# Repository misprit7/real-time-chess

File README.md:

<h1 align="center">
  <!--<picture></picture>-->
  <br />
  Real Time Chess
</h1>
<h2 align="center">
  A physical chess board without the concept of turns
</h2>
<h2 align="center">
  Video explanation: https://youtu.be/y7VtSK23_Jg
</h2>

# Pitch

Chess is boring. I'm boring too so I enjoy it anyways, but I can't help but think "I could design it better." Normally in chess players move sequentially in turns, but this introduces a huge latency bug that the developers of chess forgot to patch: you spend literally half the time waiting for your opponent!

The obvious solution is just get rid of the concept of turns in chess altogether and let players move whenever they want. Real time strategy games like StarCraft and Age of Empires are much more fun and spectator friendly than chess, so this should be a pretty uncontroversial minor rules update that can be implemented before the next world championship. To prevent things from getting too chaotic over the board each piece has an individual cooldown, so once it's been moved it can't move for a fixed period afterwards.

However there's an unfortunate roadblock to the widespread adoption of real time chess: as the [Niemann controversy](https://www.cnn.com/2023/09/26/sport/hans-niemann-denies-sex-toys-cheating-chess-spt-intl/index.html) has made all too clear, chess is [not immune](https://www.youtube.com/watch?v=QNuu8KTUEwU) from accusations of cheating through spectator **ass**istance or outside **anal**isys tools. Trying to have players self enforce these piece cooldowns is impossible. However where the intrinsic goodness of the human psyche fails, engineering is always ready to step in. This project is a physical chess board that keeps track and displays the cooldown remaining for each piece, and even physically holds them in place so no accidental cheating can occur.

# Design Files

The firmware and pcb kicad files are in this repo. For the physical design, see [the design on OnShape](https://cad.onshape.com/documents/ad9a4c8f8eed1cb460895551/w/e793072796f18b5ae284597f/e/b7ae406cfa566c5c0e6fed4b). Other than those parts that were cnced, here were the off the shelf components used:

- [Insulating washers](https://www.mcmaster.com/catalog/130/3683/95225A340): One under each electromagnet, to keep them isolated from the casing
- [Plastic screws](https://www.mcmaster.com/catalog/130/3446/92492A728): To attach electromagnets to base, plastic to prevent electrical connection
- [These](https://www.mcmaster.com/catalog/130/3435/92095A182) and [these](https://www.mcmaster.com/catalog/130/3435/92095A177) screws: to attach the internal supports and squares respectively
- [Spacers](https://www.mcmaster.com/catalog/94669A095): For an offset between the decorative and functional pcbs
- [Electromagnets](https://www.adafruit.com/product/3873): Most expensive part other than the machining, ~$600 per board. Could probably get them cheaper from China or something but for low quantities this was easiest

# Known Issues

- Power distribution: Traces on the pcbs are way undersized given there are many amps running through them, so there are large voltage drops when many pieces are on cooldown simultaneously. To solve this these traces should be much wider
- Tolerances: The pcbs have extremely tight tolerances which makes assmbling the board extremely annoying. The edges and holes should probably have more room
- Pin heights: The height of the pins for the banana connectors are taller than the mechanical design allows for, these are fairly easy to shorten using a dremel but probably something that should be fixed
- Corner screws: Given the order of assembly, it's impossible to insert/fasten the 4 corner screws

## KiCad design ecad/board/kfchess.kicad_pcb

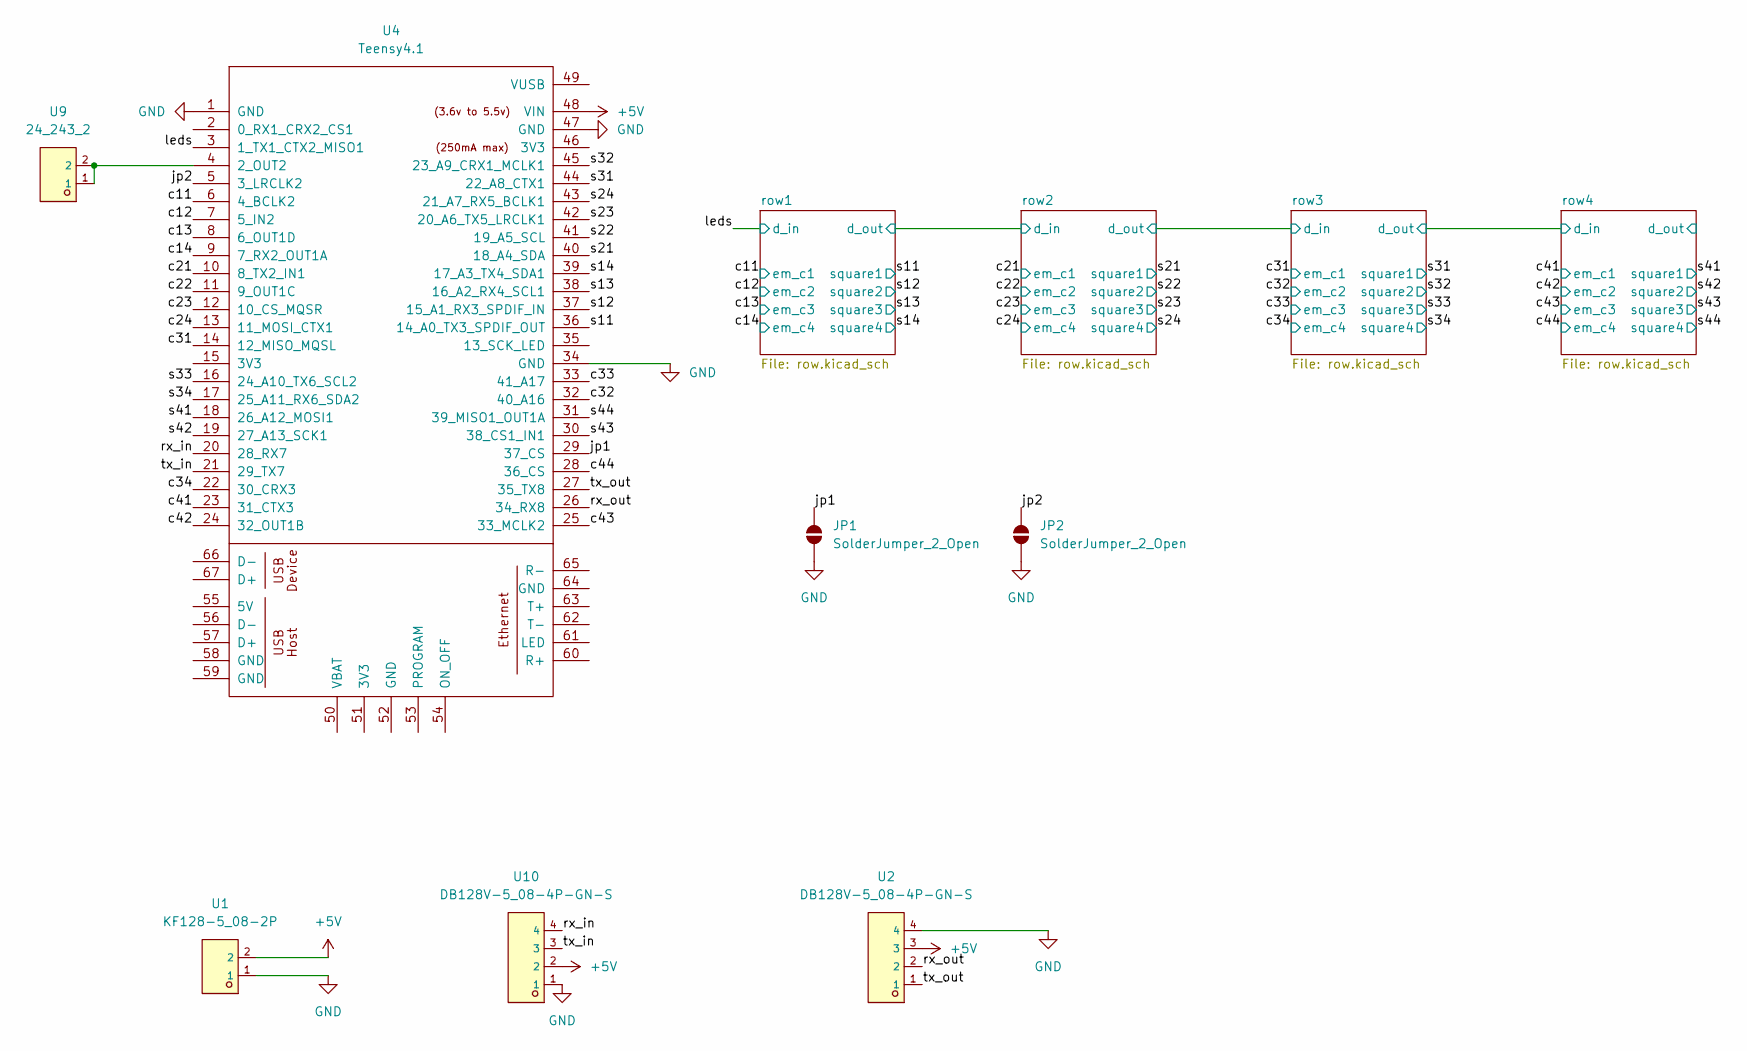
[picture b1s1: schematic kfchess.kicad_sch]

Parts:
JP1, JP2: SolderJumper_2_Open; SolderJumper-2_P1.3mm_Open_Pad1.0x1.5mm
U1: KF128-5_08-2P; CONN-TH_P5.08_KF128-5.08-2P; LCSC C474952
U2, U10: DB128V-5_08-4P-GN-S; CONN-TH_4P-P5.08_DIBO_DB128V-5.08; LCSC C2915641
U4: Teensy4.1; Teensy41
U9: 24_243_2; CONN-TH_24.243.2; LCSC C7437322

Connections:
+5V: U1.2, U2.3, U4.48 (VIN), U10.2; also elsewhere on the board
/c11: U4.6 (4_BCLK2); also elsewhere on the board
/c12: U4.7 (5_IN2); also elsewhere on the board
/c13: U4.8 (6_OUT1D); also elsewhere on the board
/c14: U4.9 (7_RX2_OUT1A); also elsewhere on the board
/c21: U4.10 (8_TX2_IN1); also elsewhere on the board
/c22: U4.11 (9_OUT1C); also elsewhere on the board
/c23: U4.12 (10_CS_MQSR); also elsewhere on the board
/c24: U4.13 (11_MOSI_CTX1); also elsewhere on the board
/c31: U4.14 (12_MISO_MQSL); also elsewhere on the board
/c32: U4.32 (40_A16); also elsewhere on the board
/c33: U4.33 (41_A17); also elsewhere on the board
/c34: U4.22 (30_CRX3); also elsewhere on the board
/c41: U4.23 (31_CTX3); also elsewhere on the board
/c42: U4.24 (32_OUT1B); also elsewhere on the board
/c43: U4.25 (33_MCLK2); also elsewhere on the board
/c44: U4.28 (36_CS); also elsewhere on the board
/jp1: JP1.2 (B), U4.29 (37_CS)
/jp2: JP2.2 (B), U4.5 (3_LRCLK2)
/leds: U4.3 (1_TX1_CTX2_MISO1); also elsewhere on the board
/rx_in: U4.20 (28_RX7), U10.4
/rx_out: U2.2, U4.26 (34_RX8)
/s11: U4.36 (14_A0_TX3_SPDIF_OUT); also elsewhere on the board
/s13: U4.38 (16_A2_RX4_SCL1); also elsewhere on the board
/s14: U4.39 (17_A3_TX4_SDA1); also elsewhere on the board
/s21: U4.40 (18_A4_SDA); also elsewhere on the board
/s22: U4.41 (19_A5_SCL); also elsewhere on the board
/s24: U4.43 (21_A7_RX5_BCLK1); also elsewhere on the board
/s31: U4.44 (22_A8_CTX1); also elsewhere on the board
/s32: U4.45 (23_A9_CRX1_MCLK1); also elsewhere on the board
/s33: U4.16 (24_A10_TX6_SCL2); also elsewhere on the board
/s34: U4.17 (25_A11_RX6_SDA2); also elsewhere on the board
/s41: U4.18 (26_A12_MOSI1); also elsewhere on the board
/s42: U4.19 (27_A13_SCK1); also elsewhere on the board
/s43: U4.30 (38_CS1_IN1); also elsewhere on the board
/s44: U4.31 (39_MISO1_OUT1A); also elsewhere on the board
/tx_in: U4.21 (29_TX7), U10.3
/tx_out: U2.1, U4.27 (35_TX8)
GND: JP1.1 (A), JP2.1 (A), U1.1, U2.4, U4.1 (GND), U4.34 (GND), U4.47 (GND), U10.1; also elsewhere on the board
unnamed: U4.4 (2_OUT2), U9.1, U9.2

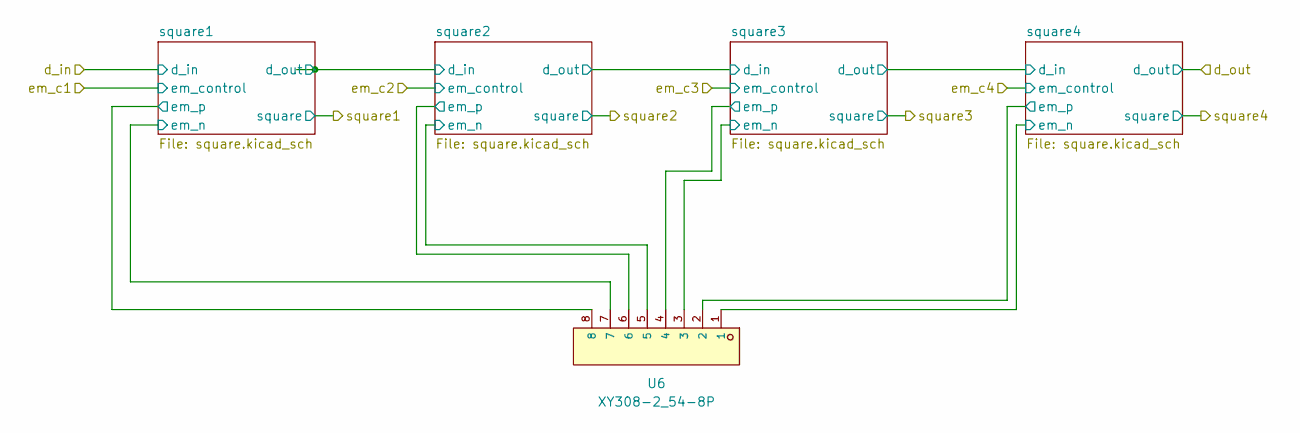
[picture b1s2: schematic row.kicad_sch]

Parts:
U6: XY308-2_54-8P; CONN-TH_XY308-2.54-8P; LCSC C915917

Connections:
+5V: U6.2, U6.4, U6.6, U6.8; also elsewhere on the board
/row2/square1/em_n: U6.7; also elsewhere on the board
/row2/square2/em_n: U6.5; also elsewhere on the board
/row2/square4/em_n: U6.1; also elsewhere on the board

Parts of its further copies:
U5, U7, U8: XY308-2_54-8P; CONN-TH_XY308-2.54-8P; LCSC C915917

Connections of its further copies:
+5V: U5.2, U5.4, U5.6, U5.8, U7.2, U7.4, U7.6, U7.8, U8.2, U8.4, U8.6, U8.8; also elsewhere on the board
/row1/square1/em_n: U5.7; also elsewhere on the board
/row1/square3/em_n: U5.3; also elsewhere on the board
/row1/square4/em_n: U5.1; also elsewhere on the board
/row3/square1/em_n: U7.7; also elsewhere on the board
/row3/square2/em_n: U7.5; also elsewhere on the board
/row3/square3/em_n: U7.3; also elsewhere on the board
/row3/square4/em_n: U7.1; also elsewhere on the board
/row4/square1/em_n: U8.7; also elsewhere on the board
/row4/square2/em_n: U8.5; also elsewhere on the board
/row4/square3/em_n: U8.3; also elsewhere on the board
/row4/square4/em_n: U8.1; also elsewhere on the board

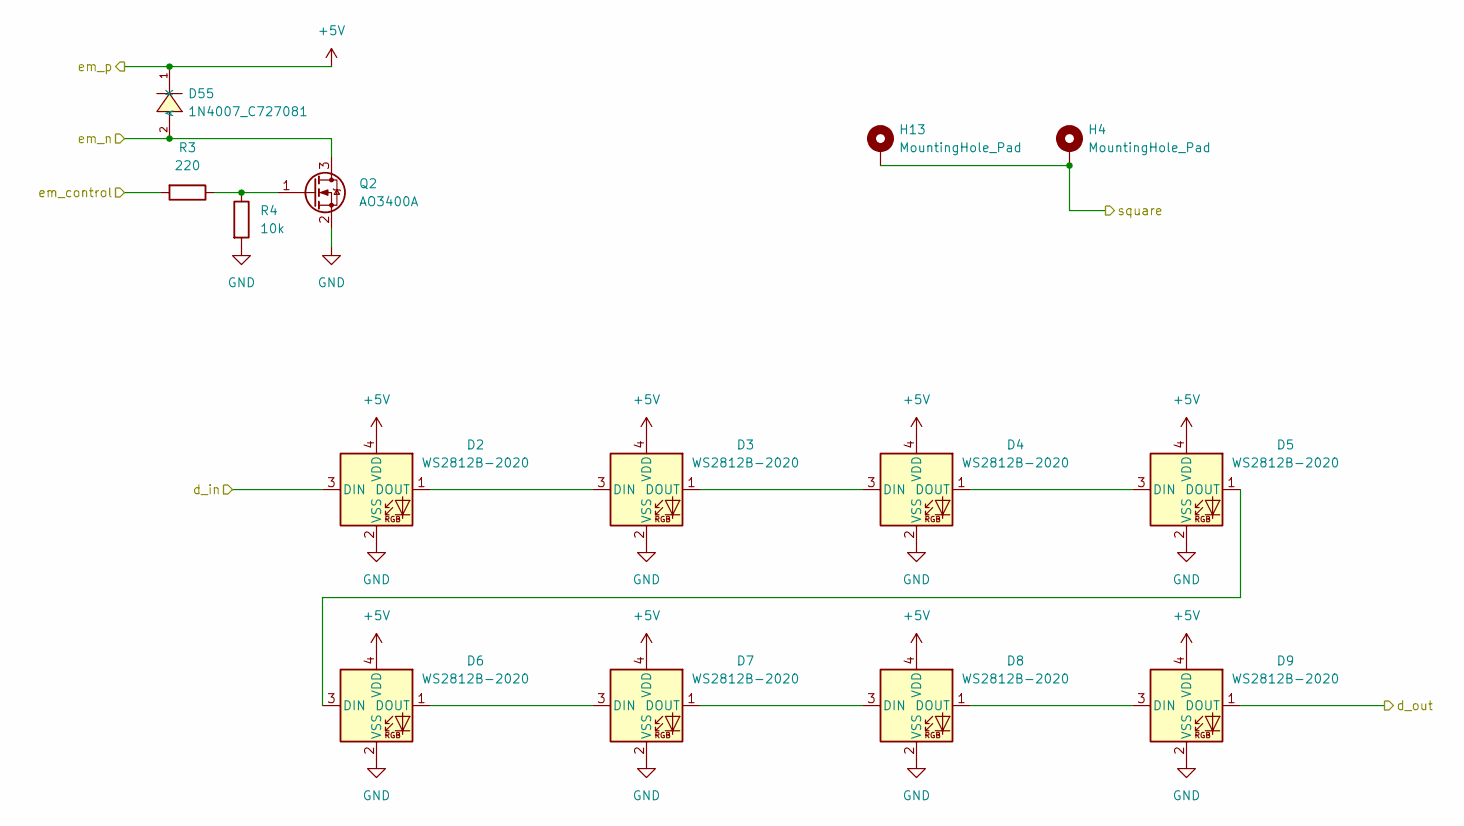
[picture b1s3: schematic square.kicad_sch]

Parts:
D2, D3, D4, D5, D6, D7, D8, D9: WS2812B-2020; LED_WS2812B-2020_PLCC4_2.0x2.0mm
D55: 1N4007_C727081; SMA_L4.3-W2.5-LS5.0-RD; LCSC C727081
H4, H13: MountingHole_Pad; MountingHole_3.2mm_M3_Pad
Q2: AO3400A; SOT-23
R3: 220; R_0603_1608Metric
R4: 10k; R_0603_1608Metric

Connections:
+5V: D2.4 (VDD), D3.4 (VDD), D4.4 (VDD), D5.4 (VDD), D6.4 (VDD), D7.4 (VDD), D8.4 (VDD), D9.4 (VDD), D55.1 (K); also elsewhere on the board
/c12: R3.2; also elsewhere on the board
/leds: D2.3 (DIN); also elsewhere on the board
/row1/square1/d_out: D9.1 (DOUT); also elsewhere on the board
GND: D2.2 (VSS), D3.2 (VSS), D4.2 (VSS), D5.2 (VSS), D6.2 (VSS), D7.2 (VSS), D8.2 (VSS), D9.2 (VSS), Q2.2 (S), R4.2; also elsewhere on the board
unnamed: D2.1 (DOUT), D3.3 (DIN)
unnamed: D3.1 (DOUT), D4.3 (DIN)
unnamed: D4.1 (DOUT), D5.3 (DIN)
unnamed: D5.1 (DOUT), D6.3 (DIN)
unnamed: D6.1 (DOUT), D7.3 (DIN)
unnamed: D7.1 (DOUT), D8.3 (DIN)
unnamed: D8.1 (DOUT), D9.3 (DIN)
unnamed: Q2.1 (G), R3.1, R4.1

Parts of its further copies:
D1, D10, D19, D28, D37, D46, D64, D73, D82, D91, D100, D109, D118, D127, D136: 1N4007_C727081; SMA_L4.3-W2.5-LS5.0-RD; LCSC C727081
D11, D12, D13, D14, D15, D16, D17, D18, D20, D21, D22, D23, D24, D25, D26, D27, D29, D30, D31, D32, D33, D34, D35, D36, D38, D39, D40, D41, D42, D43, D44, D45, D47, D48, D49, D50, D51, D52, D53, D54, D56, D57, D58, D59, D60, D61, D62, D63, D65, D66, D67, D68, D69, D70, D71, D72, D74, D75, D76, D77, D78, D79, D80, D81, D83, D84, D85, D86, D87, D88, D89, D90, D92, D93, D94, D95, D96, D97, D98, D99, D101, D102, D103, D104, D105, D106, D107, D108, D110, D111, D112, D113, D114, D115, D116, D117, D119, D120, D121, D122, D123, D124, D125, D126, D128, D129, D130, D131, D132, D133, D134, D135, D137, D138, D139, D140, D141, D142, D143, D144: WS2812B-2020; LED_WS2812B-2020_PLCC4_2.0x2.0mm
H1, H2, H3, H5, H6, H7, H8, H9, H10, H11, H12, H14, H15, H16, H17, H18, H19, H20, H21, H22, H23, H24, H25, H26, H27, H28, H29, H30, H31, H32: MountingHole_Pad; MountingHole_3.2mm_M3_Pad
Q1, Q3, Q4, Q5, Q6, Q7, Q8, Q9, Q10, Q11, Q12, Q13, Q14, Q15, Q16: AO3400A; SOT-23
R1, R5, R7, R9, R11, R13, R15, R17, R19, R21, R23, R25, R27, R29, R31: 220; R_0603_1608Metric
R2, R6, R8, R10, R12, R14, R16, R18, R20, R22, R24, R26, R28, R30, R32: 10k; R_0603_1608Metric

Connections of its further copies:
+5V: D1.1 (K), D10.1 (K), D11.4 (VDD), D12.4 (VDD), D13.4 (VDD), D14.4 (VDD), D15.4 (VDD), D16.4 (VDD), D17.4 (VDD), D18.4 (VDD), D19.1 (K), D20.4 (VDD), D21.4 (VDD), D22.4 (VDD), D23.4 (VDD), D24.4 (VDD), D25.4 (VDD), D26.4 (VDD), D27.4 (VDD), D28.1 (K), D29.4 (VDD), D30.4 (VDD), D31.4 (VDD), D32.4 (VDD), D33.4 (VDD), D34.4 (VDD), D35.4 (VDD), D36.4 (VDD), D37.1 (K), D38.4 (VDD), D39.4 (VDD), D40.4 (VDD), D41.4 (VDD), D42.4 (VDD), D43.4 (VDD), D44.4 (VDD), D45.4 (VDD), D46.1 (K), D47.4 (VDD), D48.4 (VDD), D49.4 (VDD), D50.4 (VDD), D51.4 (VDD), D52.4 (VDD), D53.4 (VDD), D54.4 (VDD), D56.4 (VDD), D57.4 (VDD), D58.4 (VDD), D59.4 (VDD), D60.4 (VDD), D61.4 (VDD), D62.4 (VDD), D63.4 (VDD), D64.1 (K), D65.4 (VDD), D66.4 (VDD), D67.4 (VDD), D68.4 (VDD), D69.4 (VDD), D70.4 (VDD), D71.4 (VDD), D72.4 (VDD), D73.1 (K), D74.4 (VDD), D75.4 (VDD), D76.4 (VDD), D77.4 (VDD), D78.4 (VDD), D79.4 (VDD), D80.4 (VDD), D81.4 (VDD), D82.1 (K), D83.4 (VDD), D84.4 (VDD), D85.4 (VDD), D86.4 (VDD), D87.4 (VDD), D88.4 (VDD), D89.4 (VDD), D90.4 (VDD), D91.1 (K), D92.4 (VDD), D93.4 (VDD), D94.4 (VDD), D95.4 (VDD), D96.4 (VDD), D97.4 (VDD), D98.4 (VDD), D99.4 (VDD), D100.1 (K), D101.4 (VDD), D102.4 (VDD), D103.4 (VDD), D104.4 (VDD), D105.4 (VDD), D106.4 (VDD), D107.4 (VDD), D108.4 (VDD), D109.1 (K), D110.4 (VDD), D111.4 (VDD), D112.4 (VDD), D113.4 (VDD), D114.4 (VDD), D115.4 (VDD), D116.4 (VDD), D117.4 (VDD), D118.1 (K), D119.4 (VDD), D120.4 (VDD), D121.4 (VDD), D122.4 (VDD), D123.4 (VDD), D124.4 (VDD), D125.4 (VDD), D126.4 (VDD), D127.1 (K), D128.4 (VDD), D129.4 (VDD), D130.4 (VDD), D131.4 (VDD), D132.4 (VDD), D133.4 (VDD), D134.4 (VDD), D135.4 (VDD), D136.1 (K), D137.4 (VDD), D138.4 (VDD), D139.4 (VDD), D140.4 (VDD), D141.4 (VDD), D142.4 (VDD), D143.4 (VDD), D144.4 (VDD); also elsewhere on the board
/c11: R1.2; also elsewhere on the board
/c13: R5.2; also elsewhere on the board
/c14: R7.2; also elsewhere on the board
/c21: R9.2; also elsewhere on the board
/c22: R11.2; also elsewhere on the board
/c23: R13.2; also elsewhere on the board
/c24: R15.2; also elsewhere on the board
/c31: R17.2; also elsewhere on the board
/c32: R19.2; also elsewhere on the board
/c33: R21.2; also elsewhere on the board
/c34: R23.2; also elsewhere on the board
/c41: R25.2; also elsewhere on the board
/c42: R27.2; also elsewhere on the board
/c43: R29.2; also elsewhere on the board
/c44: R31.2; also elsewhere on the board
/row1/d_out: D36.1 (DOUT), D38.3 (DIN)
/row1/square1/d_out: D11.3 (DIN); also elsewhere on the board
/row1/square1/em_n: D1.2 (A), Q1.3 (D); also elsewhere on the board
/row1/square2/d_out: D18.1 (DOUT), D20.3 (DIN)
/row1/square3/d_out: D27.1 (DOUT), D29.3 (DIN)
/row1/square3/em_n: D19.2 (A), Q3.3 (D); also elsewhere on the board
/row1/square4/em_n: D28.2 (A), Q4.3 (D); also elsewhere on the board
/row2/d_out: D72.1 (DOUT), D74.3 (DIN)
/row2/square1/d_out: D45.1 (DOUT), D47.3 (DIN)
/row2/square1/em_n: D37.2 (A), Q5.3 (D); also elsewhere on the board
/row2/square2/d_out: D54.1 (DOUT), D56.3 (DIN)
/row2/square2/em_n: D46.2 (A), Q6.3 (D); also elsewhere on the board
/row2/square3/d_out: D63.1 (DOUT), D65.3 (DIN)
/row2/square4/em_n: D64.2 (A), Q8.3 (D); also elsewhere on the board
/row3/d_out: D108.1 (DOUT), D110.3 (DIN)
/row3/square1/d_out: D81.1 (DOUT), D83.3 (DIN)
/row3/square1/em_n: D73.2 (A), Q9.3 (D); also elsewhere on the board
/row3/square2/d_out: D90.1 (DOUT), D92.3 (DIN)
/row3/square2/em_n: D82.2 (A), Q10.3 (D); also elsewhere on the board
/row3/square3/d_out: D99.1 (DOUT), D101.3 (DIN)
/row3/square3/em_n: D91.2 (A), Q11.3 (D); also elsewhere on the board
/row3/square4/em_n: D100.2 (A), Q12.3 (D); also elsewhere on the board
/row4/d_out: D144.1 (DOUT)
/row4/square1/d_out: D117.1 (DOUT), D119.3 (DIN)
/row4/square1/em_n: D109.2 (A), Q13.3 (D); also elsewhere on the board
/row4/square2/d_out: D126.1 (DOUT), D128.3 (DIN)
/row4/square2/em_n: D118.2 (A), Q14.3 (D); also elsewhere on the board
/row4/square3/d_out: D135.1 (DOUT), D137.3 (DIN)
/row4/square3/em_n: D127.2 (A), Q15.3 (D); also elsewhere on the board
/row4/square4/em_n: D136.2 (A), Q16.3 (D); also elsewhere on the board
/s11: H1.1, H2.1; also elsewhere on the board
/s13: H5.1, H6.1; also elsewhere on the board
/s14: H7.1, H8.1; also elsewhere on the board
/s21: H9.1, H10.1; also elsewhere on the board
/s22: H11.1, H12.1; also elsewhere on the board
/s24: H15.1, H16.1; also elsewhere on the board
/s31: H17.1, H18.1; also elsewhere on the board
/s32: H19.1, H20.1; also elsewhere on the board
/s33: H21.1, H22.1; also elsewhere on the board
/s34: H23.1, H24.1; also elsewhere on the board
/s41: H25.1, H26.1; also elsewhere on the board
/s42: H27.1, H28.1; also elsewhere on the board
/s43: H29.1, H30.1; also elsewhere on the board
/s44: H31.1, H32.1; also elsewhere on the board
GND: D11.2 (VSS), D12.2 (VSS), D13.2 (VSS), D14.2 (VSS), D15.2 (VSS), D16.2 (VSS), D17.2 (VSS), D18.2 (VSS), D20.2 (VSS), D21.2 (VSS), D22.2 (VSS), D23.2 (VSS), D24.2 (VSS), D25.2 (VSS), D26.2 (VSS), D27.2 (VSS), D29.2 (VSS), D30.2 (VSS), D31.2 (VSS), D32.2 (VSS), D33.2 (VSS), D34.2 (VSS), D35.2 (VSS), D36.2 (VSS), D38.2 (VSS), D39.2 (VSS), D40.2 (VSS), D41.2 (VSS), D42.2 (VSS), D43.2 (VSS), D44.2 (VSS), D45.2 (VSS), D47.2 (VSS), D48.2 (VSS), D49.2 (VSS), D50.2 (VSS), D51.2 (VSS), D52.2 (VSS), D53.2 (VSS), D54.2 (VSS), D56.2 (VSS), D57.2 (VSS), D58.2 (VSS), D59.2 (VSS), D60.2 (VSS), D61.2 (VSS), D62.2 (VSS), D63.2 (VSS), D65.2 (VSS), D66.2 (VSS), D67.2 (VSS), D68.2 (VSS), D69.2 (VSS), D70.2 (VSS), D71.2 (VSS), D72.2 (VSS), D74.2 (VSS), D75.2 (VSS), D76.2 (VSS), D77.2 (VSS), D78.2 (VSS), D79.2 (VSS), D80.2 (VSS), D81.2 (VSS), D83.2 (VSS), D84.2 (VSS), D85.2 (VSS), D86.2 (VSS), D87.2 (VSS), D88.2 (VSS), D89.2 (VSS), D90.2 (VSS), D92.2 (VSS), D93.2 (VSS), D94.2 (VSS), D95.2 (VSS), D96.2 (VSS), D97.2 (VSS), D98.2 (VSS), D99.2 (VSS), D101.2 (VSS), D102.2 (VSS), D103.2 (VSS), D104.2 (VSS), D105.2 (VSS), D106.2 (VSS), D107.2 (VSS), D108.2 (VSS), D110.2 (VSS), D111.2 (VSS), D112.2 (VSS), D113.2 (VSS), D114.2 (VSS), D115.2 (VSS), D116.2 (VSS), D117.2 (VSS), D119.2 (VSS), D120.2 (VSS), D121.2 (VSS), D122.2 (VSS), D123.2 (VSS), D124.2 (VSS), D125.2 (VSS), D126.2 (VSS), D128.2 (VSS), D129.2 (VSS), D130.2 (VSS), D131.2 (VSS), D132.2 (VSS), D133.2 (VSS), D134.2 (VSS), D135.2 (VSS), D137.2 (VSS), D138.2 (VSS), D139.2 (VSS), D140.2 (VSS), D141.2 (VSS), D142.2 (VSS), D143.2 (VSS), D144.2 (VSS), Q1.2 (S), Q3.2 (S), Q4.2 (S), Q5.2 (S), Q6.2 (S), Q7.2 (S), Q8.2 (S), Q9.2 (S), Q10.2 (S), Q11.2 (S), Q12.2 (S), Q13.2 (S), Q14.2 (S), Q15.2 (S), Q16.2 (S), R2.2, R6.2, R8.2, R10.2, R12.2, R14.2, R16.2, R18.2, R20.2, R22.2, R24.2, R26.2, R28.2, R30.2, R32.2; also elsewhere on the board
unnamed: D11.1 (DOUT), D12.3 (DIN)
unnamed: D12.1 (DOUT), D13.3 (DIN)
unnamed: D13.1 (DOUT), D14.3 (DIN)
unnamed: D14.1 (DOUT), D15.3 (DIN)
unnamed: D15.1 (DOUT), D16.3 (DIN)
unnamed: D16.1 (DOUT), D17.3 (DIN)
unnamed: D17.1 (DOUT), D18.3 (DIN)
unnamed: D20.1 (DOUT), D21.3 (DIN)
unnamed: D21.1 (DOUT), D22.3 (DIN)
unnamed: D22.1 (DOUT), D23.3 (DIN)
unnamed: D23.1 (DOUT), D24.3 (DIN)
unnamed: D24.1 (DOUT), D25.3 (DIN)
unnamed: D25.1 (DOUT), D26.3 (DIN)
unnamed: D26.1 (DOUT), D27.3 (DIN)
unnamed: D29.1 (DOUT), D30.3 (DIN)
unnamed: D30.1 (DOUT), D31.3 (DIN)
unnamed: D31.1 (DOUT), D32.3 (DIN)
unnamed: D32.1 (DOUT), D33.3 (DIN)
unnamed: D33.1 (DOUT), D34.3 (DIN)
unnamed: D34.1 (DOUT), D35.3 (DIN)
unnamed: D35.1 (DOUT), D36.3 (DIN)
unnamed: D38.1 (DOUT), D39.3 (DIN)
unnamed: D39.1 (DOUT), D40.3 (DIN)
unnamed: D40.1 (DOUT), D41.3 (DIN)
unnamed: D41.1 (DOUT), D42.3 (DIN)
unnamed: D42.1 (DOUT), D43.3 (DIN)
unnamed: D43.1 (DOUT), D44.3 (DIN)
unnamed: D44.1 (DOUT), D45.3 (DIN)
unnamed: D47.1 (DOUT), D48.3 (DIN)
unnamed: D48.1 (DOUT), D49.3 (DIN)
unnamed: D49.1 (DOUT), D50.3 (DIN)
unnamed: D50.1 (DOUT), D51.3 (DIN)
unnamed: D51.1 (DOUT), D52.3 (DIN)
unnamed: D52.1 (DOUT), D53.3 (DIN)
unnamed: D53.1 (DOUT), D54.3 (DIN)
unnamed: D56.1 (DOUT), D57.3 (DIN)
unnamed: D57.1 (DOUT), D58.3 (DIN)
unnamed: D58.1 (DOUT), D59.3 (DIN)
unnamed: D59.1 (DOUT), D60.3 (DIN)
unnamed: D60.1 (DOUT), D61.3 (DIN)
unnamed: D61.1 (DOUT), D62.3 (DIN)
unnamed: D62.1 (DOUT), D63.3 (DIN)
unnamed: D65.1 (DOUT), D66.3 (DIN)
unnamed: D66.1 (DOUT), D67.3 (DIN)
unnamed: D67.1 (DOUT), D68.3 (DIN)
unnamed: D68.1 (DOUT), D69.3 (DIN)
unnamed: D69.1 (DOUT), D70.3 (DIN)
unnamed: D70.1 (DOUT), D71.3 (DIN)
unnamed: D71.1 (DOUT), D72.3 (DIN)
unnamed: D74.1 (DOUT), D75.3 (DIN)
unnamed: D75.1 (DOUT), D76.3 (DIN)
unnamed: D76.1 (DOUT), D77.3 (DIN)
unnamed: D77.1 (DOUT), D78.3 (DIN)
unnamed: D78.1 (DOUT), D79.3 (DIN)
unnamed: D79.1 (DOUT), D80.3 (DIN)
unnamed: D80.1 (DOUT), D81.3 (DIN)
unnamed: D83.1 (DOUT), D84.3 (DIN)
unnamed: D84.1 (DOUT), D85.3 (DIN)
unnamed: D85.1 (DOUT), D86.3 (DIN)
unnamed: D86.1 (DOUT), D87.3 (DIN)
unnamed: D87.1 (DOUT), D88.3 (DIN)
unnamed: D88.1 (DOUT), D89.3 (DIN)
unnamed: D89.1 (DOUT), D90.3 (DIN)
unnamed: D92.1 (DOUT), D93.3 (DIN)
unnamed: D93.1 (DOUT), D94.3 (DIN)
unnamed: D94.1 (DOUT), D95.3 (DIN)
unnamed: D95.1 (DOUT), D96.3 (DIN)
unnamed: D96.1 (DOUT), D97.3 (DIN)
unnamed: D97.1 (DOUT), D98.3 (DIN)
unnamed: D98.1 (DOUT), D99.3 (DIN)
unnamed: D101.1 (DOUT), D102.3 (DIN)
unnamed: D102.1 (DOUT), D103.3 (DIN)
unnamed: D103.1 (DOUT), D104.3 (DIN)
unnamed: D104.1 (DOUT), D105.3 (DIN)
unnamed: D105.1 (DOUT), D106.3 (DIN)
unnamed: D106.1 (DOUT), D107.3 (DIN)
unnamed: D107.1 (DOUT), D108.3 (DIN)
unnamed: D110.1 (DOUT), D111.3 (DIN)
unnamed: D111.1 (DOUT), D112.3 (DIN)
unnamed: D112.1 (DOUT), D113.3 (DIN)
unnamed: D113.1 (DOUT), D114.3 (DIN)
unnamed: D114.1 (DOUT), D115.3 (DIN)
unnamed: D115.1 (DOUT), D116.3 (DIN)
unnamed: D116.1 (DOUT), D117.3 (DIN)
unnamed: D119.1 (DOUT), D120.3 (DIN)
unnamed: D120.1 (DOUT), D121.3 (DIN)
unnamed: D121.1 (DOUT), D122.3 (DIN)
unnamed: D122.1 (DOUT), D123.3 (DIN)
unnamed: D123.1 (DOUT), D124.3 (DIN)
unnamed: D124.1 (DOUT), D125.3 (DIN)
unnamed: D125.1 (DOUT), D126.3 (DIN)
unnamed: D128.1 (DOUT), D129.3 (DIN)
unnamed: D129.1 (DOUT), D130.3 (DIN)
unnamed: D130.1 (DOUT), D131.3 (DIN)
unnamed: D131.1 (DOUT), D132.3 (DIN)
unnamed: D132.1 (DOUT), D133.3 (DIN)
unnamed: D133.1 (DOUT), D134.3 (DIN)
unnamed: D134.1 (DOUT), D135.3 (DIN)
unnamed: D137.1 (DOUT), D138.3 (DIN)
unnamed: D138.1 (DOUT), D139.3 (DIN)
unnamed: D139.1 (DOUT), D140.3 (DIN)
unnamed: D140.1 (DOUT), D141.3 (DIN)
unnamed: D141.1 (DOUT), D142.3 (DIN)
unnamed: D142.1 (DOUT), D143.3 (DIN)
unnamed: D143.1 (DOUT), D144.3 (DIN)
unnamed: Q1.1 (G), R1.1, R2.1
unnamed: Q3.1 (G), R5.1, R6.1
unnamed: Q4.1 (G), R7.1, R8.1
unnamed: Q5.1 (G), R9.1, R10.1
unnamed: Q6.1 (G), R11.1, R12.1
unnamed: Q7.1 (G), R13.1, R14.1
unnamed: Q8.1 (G), R15.1, R16.1
unnamed: Q9.1 (G), R17.1, R18.1
unnamed: Q10.1 (G), R19.1, R20.1
unnamed: Q11.1 (G), R21.1, R22.1
unnamed: Q12.1 (G), R23.1, R24.1
unnamed: Q13.1 (G), R25.1, R26.1
unnamed: Q14.1 (G), R27.1, R28.1
unnamed: Q15.1 (G), R29.1, R30.1
unnamed: Q16.1 (G), R31.1, R32.1

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
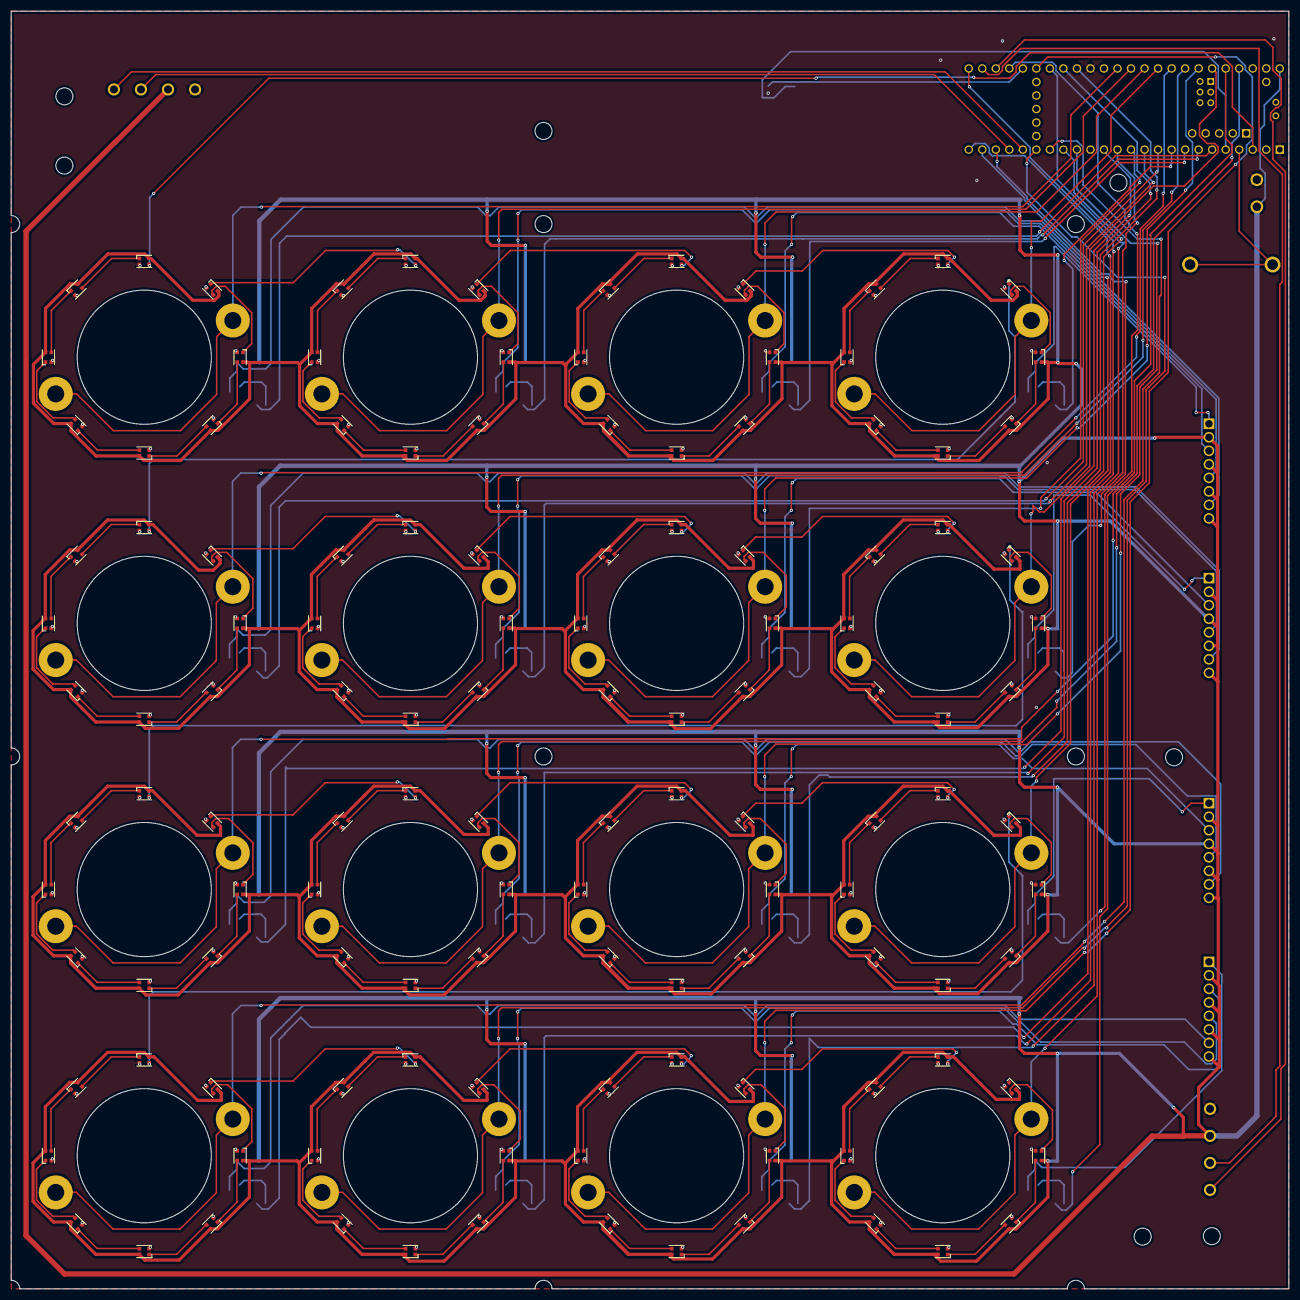
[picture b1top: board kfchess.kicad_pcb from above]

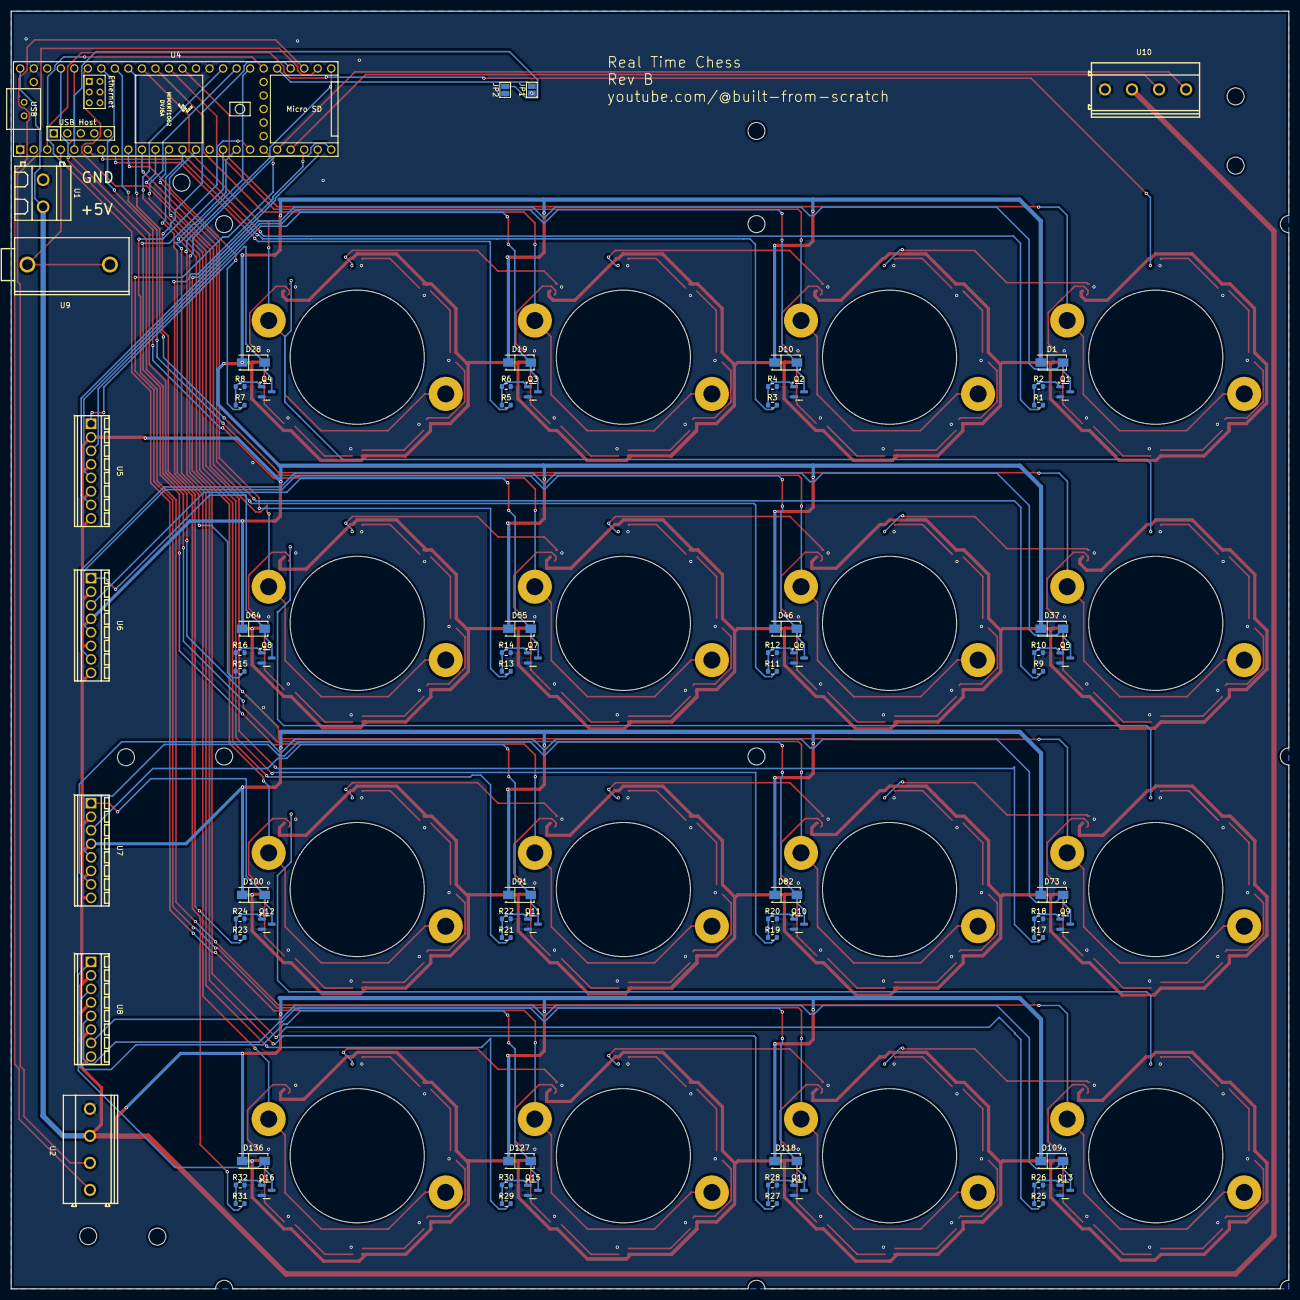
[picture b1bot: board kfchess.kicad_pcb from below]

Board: 2 copper layers, 240.0 x 240.0 mm, 235 parts (75 on the bottom side), 201 nets.

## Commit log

2024-04-06 Added fft
2024-04-06 Removed .cache
2024-04-07 Added electromagnet driver circuit
2024-04-28 Started pcb
2024-06-08 Fixed holes
2024-06-08 Started routing
2024-06-09 More routing
2024-06-09 Finished routing top squares
2024-06-10 Actually finished top
2024-06-10 Copied routing for bottom squares
2024-06-10 Tentatively finished routing
2024-06-10 Fixed errors
2024-06-10 Fixed warnings
2024-06-17 Got ws2812 leds working
2024-06-18 Reorganized directories
2024-06-18 Added readme
2024-06-19 Added freertos
2024-06-19 Cleaned up code and refactored for freertos
2024-06-19 Moved freertos into lib
2024-06-19 Added groetzel
2024-06-19 Combined led and fft tasks
2024-06-19 Fixed mutex issues with adc
2024-06-19 Added second goertzel filter
2024-06-19 Added timeout to led mutex
2024-06-20 Made detection more robust
2024-07-01 Reenabled blink
2024-07-01 Switched to new board shape
2024-07-02 New layout
2024-07-04 Finished layout
2024-07-04 Finished routing
2024-07-04 Went through and fixed drc
2024-07-04 Added edge pcbs
2024-07-04 Added logo to edge4
2024-07-04 Fixed upside down cross board screw terminals
2024-08-10 Updated pinout in firmware for revB
2024-08-21 Added jumper identification
2024-08-21 Changed sampling for new hardware
2024-08-21 Added new touch logic
2024-08-21 Added color spiral
2024-08-21 Fixed spiral
2024-08-22 Fine tuned move behavior
2024-09-06 Started UI
2024-09-30 Changed to shared square color
2024-11-10 Create LICENSE
2024-11-24 Mad subsquare addressing
2024-11-24 Fixed color spiral
2024-11-24 Made build.py
2024-11-24 Got video working
2025-03-28 Started building ui
